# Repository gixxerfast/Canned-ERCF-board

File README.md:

# Canned-ERCF-board v1.0-beta2
Enraged Rabbit Carrot Feeder CAN-FD expansion board for Duet3

The Canned ERCF board is a general purpose Duet 3 CAN extansion board but specifically made to support the [ERCF](https://github.com/EtteGit/EnragedRabbitProject) multifilament feeder system based on the [ERCF Easy Brd](https://github.com/Tircown/ERCF-easy-brd) by Tircown.

Check out the [Duet RRF ERCF macros](https://github.com/pfn/EnragedRabbitOnRRF?ref=https://coder.social) by pfn. With these macros you should be able to use a RRF equipped printer and run multi filament prints as with the original ERCF macros as long as you have enough ports and motors available.

The board uses a Atmel/Microchip SAM C21 microcontroller module with USB and CAN, the [Sammy-C21](https://www.chip45.com/products/sammy-c21-1.0_atmel_smart_arm_sam_module_samc21_usb_dual_can_duet3d.php) from [Chip45](https://www.chip45.com/).

The firmware is a modified version of the [Duet3Expansion Sammy-C21 firmware](https://github.com/Duet3D/Duet3Expansion) by [Duet3D](https://www.duet3d.com/)  

You can find the fork of the modfied Duet firmware [here](https://github.com/gixxerfast/Duet3Expansion/tree/cannedboard). As the versions are moving rapidly with the new RRF version 3.4 there's no guarantees that this will be kept in synch.

**Please note that this board will not work with the standard Duet Sammy firmware.**

The board features the following functions:

- Support for up to two TMC2209 stepsticks Stepper motor drivers with UART control
- 1500 mA 24V-5V efficient switching voltage regulator. 
- Three GPIO inputs 3.3V signal inputs that may be used for encoders and endstops with 3.3V source.
- One 3.3V PWM output for hobby micro servo control with 5V source. Note that the general advice is not to source power to the servo via the board but to have a separate 5V source.
- MCU Module. It's using the Atmel/Microchip ATSAMC21G18A based Sammy-C21 MCU-module
- Input over voltage protection up to 30V
- VIN voltage monitoring.
- Three led indicators for 3.3V, 5V and VIN (24V). Easy troubleshooting if missing a rail. 

As an extension this board has CAN-FD support and is connected to another Duet 3 board via the CAN bus. Firmware is updated via CAN and the DWC (Duet Web Control frontend) so the USB-port is not really used.

This board can be used with the Sammy-C21 Duet 3 extension board firmware together with my modified configuration file. No further modifications are required (to this date).

There's a 4.7 Kohms pullup resistor on the TX/RX UART line as the BTT TMC2209 stepsticks has a 20K ohms pulldown resistor on the same line. The Duet firmware will disable the UART line before reading and writing causing the the line to go low and therefore corrupt the UART messaging. With the 4.7 Kohms pullup resistor the line is kept high all the time and the communication can function undisturbed.

There are two pin pairs for the CAN bus so either the CAN-bus can be terminated by closing the solder brideg on the back of the board or it can be routed to the next board in the chain,

## BOM
Apart from the board as specified in the KiCad files with the SMT components which I have had mounted by JLCPCB, there a number of components needed to complete the board

- 1 x Sammy-C21 ATSAMC21G18A MCU module from [Chip45](https://www.chip45.com/) or [Filastruder](https://www.filastruder.com/products/sammy-c21-v1-0-duet3d-module)
- 2 x BTT TMC2209 stepstick modules
- 1 x LMP78_05-1.5 or compatible DC-DC voltage converter
- 2 x 16 pin PCB connection headers
- 4 x 8 pin PCB connection headers
- 2 x 2 pin PCB connection headers
- 2 x 2 pin MOLEX KK254 (or equivalent) male PCB connectors
- 4 x 3 pin Molex KK254 (or equivalent) male PCB connectors
- 2 x 4 pin Molex KK254 (or equivalent) male PCB connectors
- 1 x 2 pin Phoenix 5.08 Screw connector. Part # 277-1247-ND or eqivalent

### Disclaimer 
This is work in progress and it's right now under development and there may exist issues with this version that may or may not be corrected in the next version. It's based on many parts over which I have no control over at all. I take no responsibilty whatsoever for the functionality or safety and I claim the right to not inform about anything about this product known to me now or in the future. This is soley at your own risk and I accept no responsiblity, financially or otherwise, if it causes your controller board to break, your house to burn down, your wife to divorce you, if it simply doesn't work at all or any other scenario possible in any multiverse. If you do not accept that all responibility for use of this product is your own, please don't download, build or use it.

## License - Open hardware / Open software
This project and its content is realeased under the [GPLv3 license](https://www.gnu.org/licenses/gpl-3.0.html)

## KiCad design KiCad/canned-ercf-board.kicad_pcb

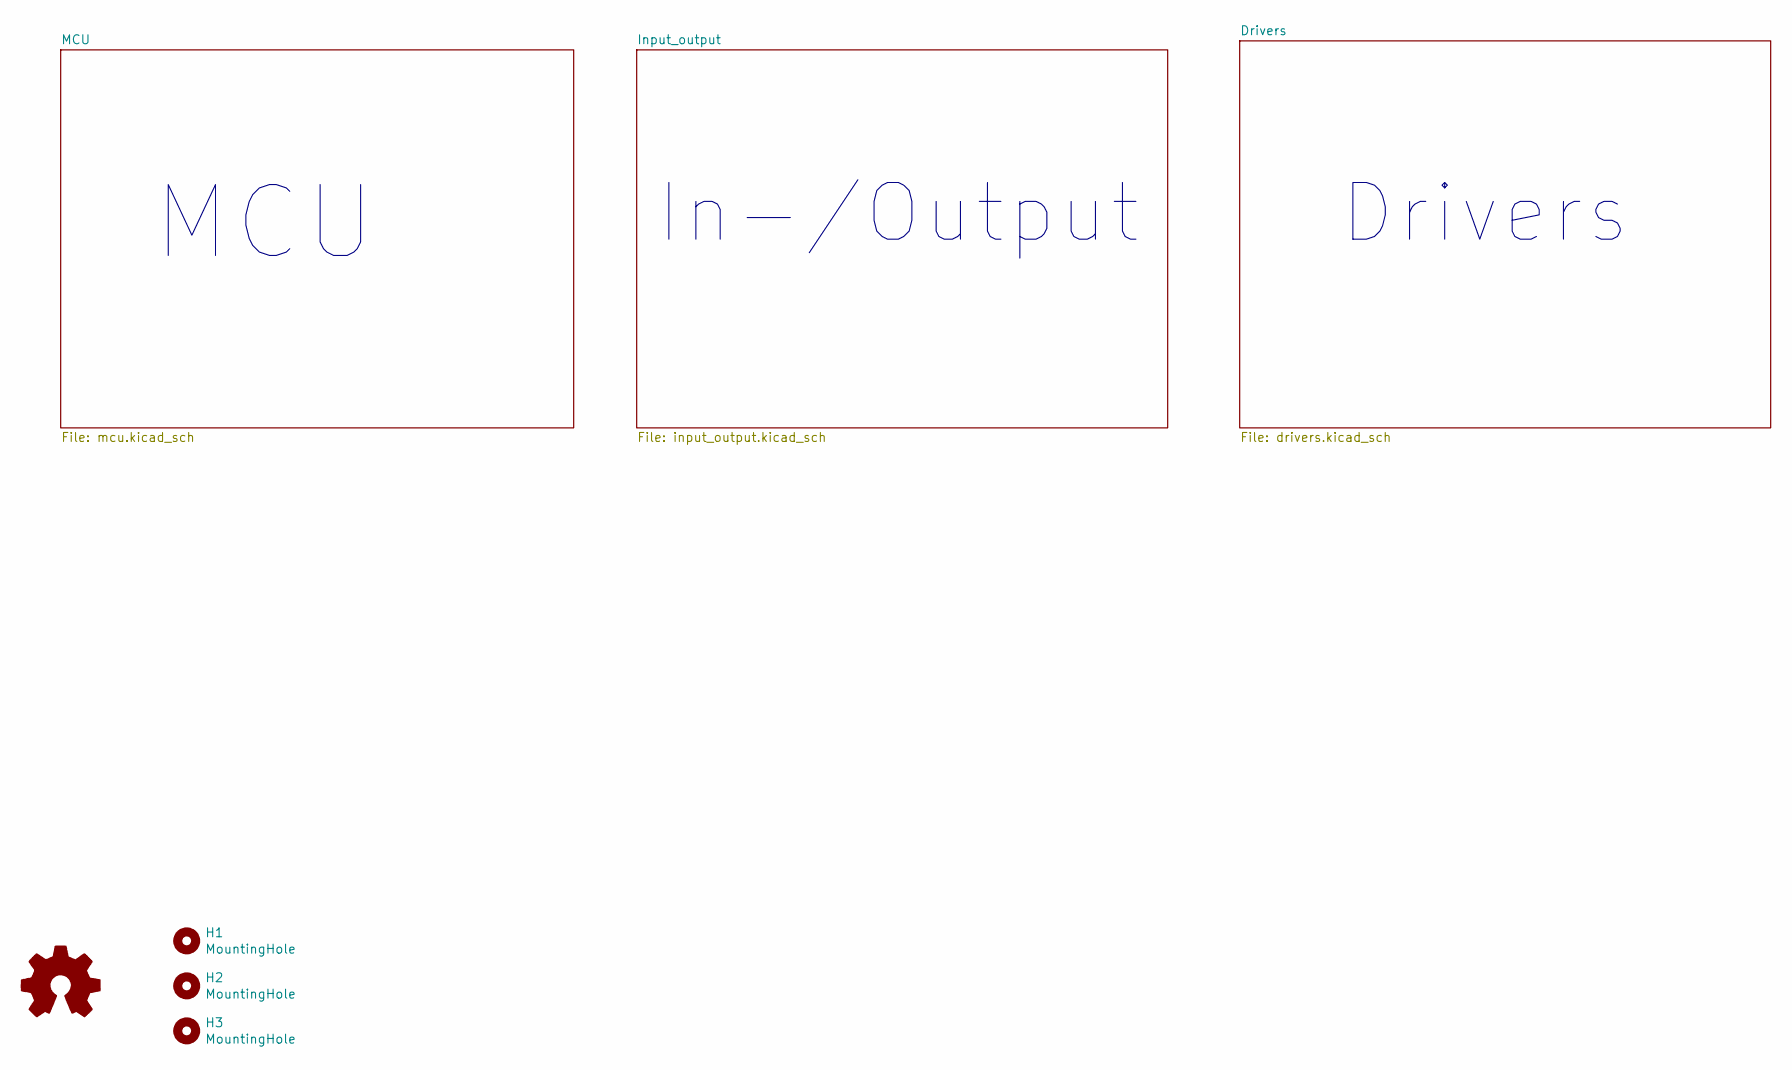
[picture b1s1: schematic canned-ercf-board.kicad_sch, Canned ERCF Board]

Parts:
H1, H2, H3: MountingHole; MountingHole_3.2mm_M3
L1: Logo_Open_Hardware_Small; OSHW-Logo2_7.3x6mm_SilkScreen

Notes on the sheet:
MCU
Drivers
In-/Output

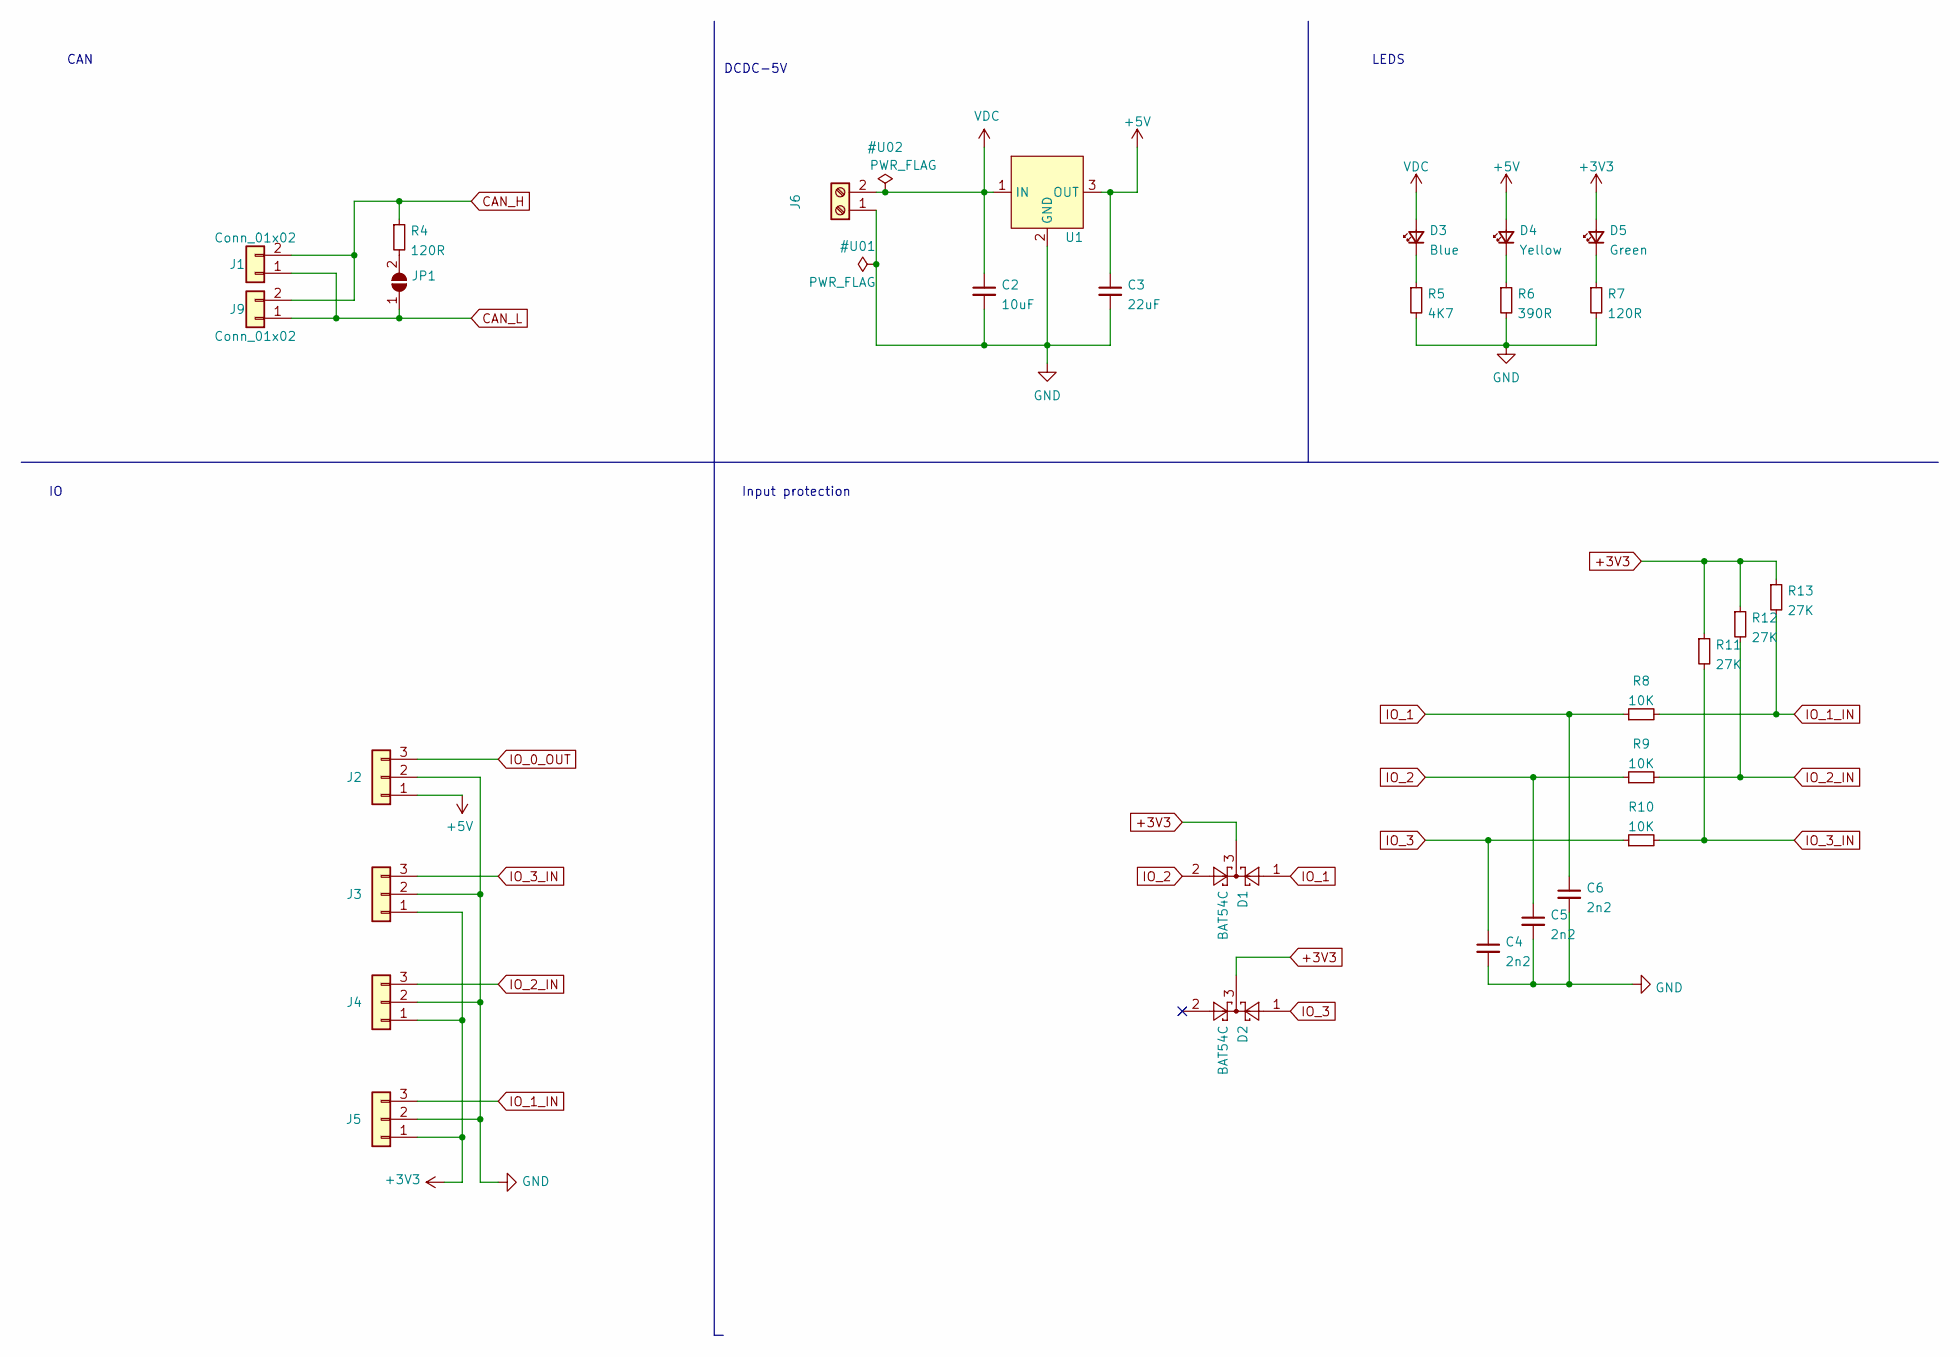
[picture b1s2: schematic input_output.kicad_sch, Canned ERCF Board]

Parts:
C2: 10uF; C_0805_2012Metric; Part GRM21BR61H106KE43L; LCSC C440198
C3: 22uF; C_0805_2012Metric; Part CL21A226MAQNNNE; LCSC C45783
C4, C5, C6: 2n2; C_0603_1608Metric; Part 0603B222K500NT; LCSC C1604
D1, D2: BAT54C; SOT-23; Part BAT54C,215; LCSC C37704
D3: Blue; LED_0603_1608Metric; Part 19-217/BHC-ZL1M2RY/3T; LCSC C72041
D4: Yellow; LED_0603_1608Metric; Part 19-213/Y2C-CQ2R2L/3T(CY); LCSC C72038
D5: Green; LED_0603_1608Metric; Part 19-217/GHC-YR1S2/3T; LCSC C72043
J1, J9: Conn_01x02; Molex_KK-254_AE-6410-02A_1x02_P2.54mm_Vertical
J2, J3, J4, J5: Conn_01x03_Male; Molex_KK-254_AE-6410-03A_1x03_P2.54mm_Vertical
J6: Screw_Terminal_01x02; TerminalBlock_bornier-2_P5.08mm_2; Part 1729128; LCSC C91153
JP1: SolderJumper_2_Open; SolderJumper-2_P1.3mm_Open_TrianglePad1.0x1.5mm
R4, R7: 120R; R_0603_1608Metric; Part 0603WAF1200T5E; LCSC C22787
R5: 4K7; R_0603_1608Metric; Part 0603WAF4701T5E; LCSC C23162
R6: 390R; R_0603_1608Metric; Part 0603WAF3900T5E; LCSC C23151
R8, R9, R10: 10K; R_0603_1608Metric; Part 0603WAF1002T5E; LCSC C25804
R11, R12, R13: 27K; R_0603_1608Metric; Part 0603WAF2702T5E; LCSC C22967
U1: Switching_Regulator_LMP78_05-1.5; Switching_regulator_POL_LMP78_1.5

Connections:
+5V: C3.1, D4.2 (A), J2.1, U1.3 (OUT); also elsewhere on the board
CAN_H: J1.2, J9.2, R4.1; also elsewhere on the board
CAN_L: J1.1, J9.1, JP1.1 (A); also elsewhere on the board
IO_0_OUT: J2.3; also elsewhere on the board
IO_1: C6.1, D1.1, R8.1; also elsewhere on the board
IO_1_IN: J5.3, R8.2, R13.2
IO_2: C5.1, D1.2, R9.1; also elsewhere on the board
IO_2_IN: J4.3, R9.2, R12.2
IO_3: C4.1, D2.1, R10.1; also elsewhere on the board
IO_3_IN: J3.3, R10.2, R11.2
unnamed: D3.1 (K), R5.1
unnamed: D4.1 (K), R6.1
unnamed: D5.1 (K), R7.1
unnamed: JP1.2 (B), R4.2

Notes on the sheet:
CAN
Input protection
LEDS
DCDC-5V

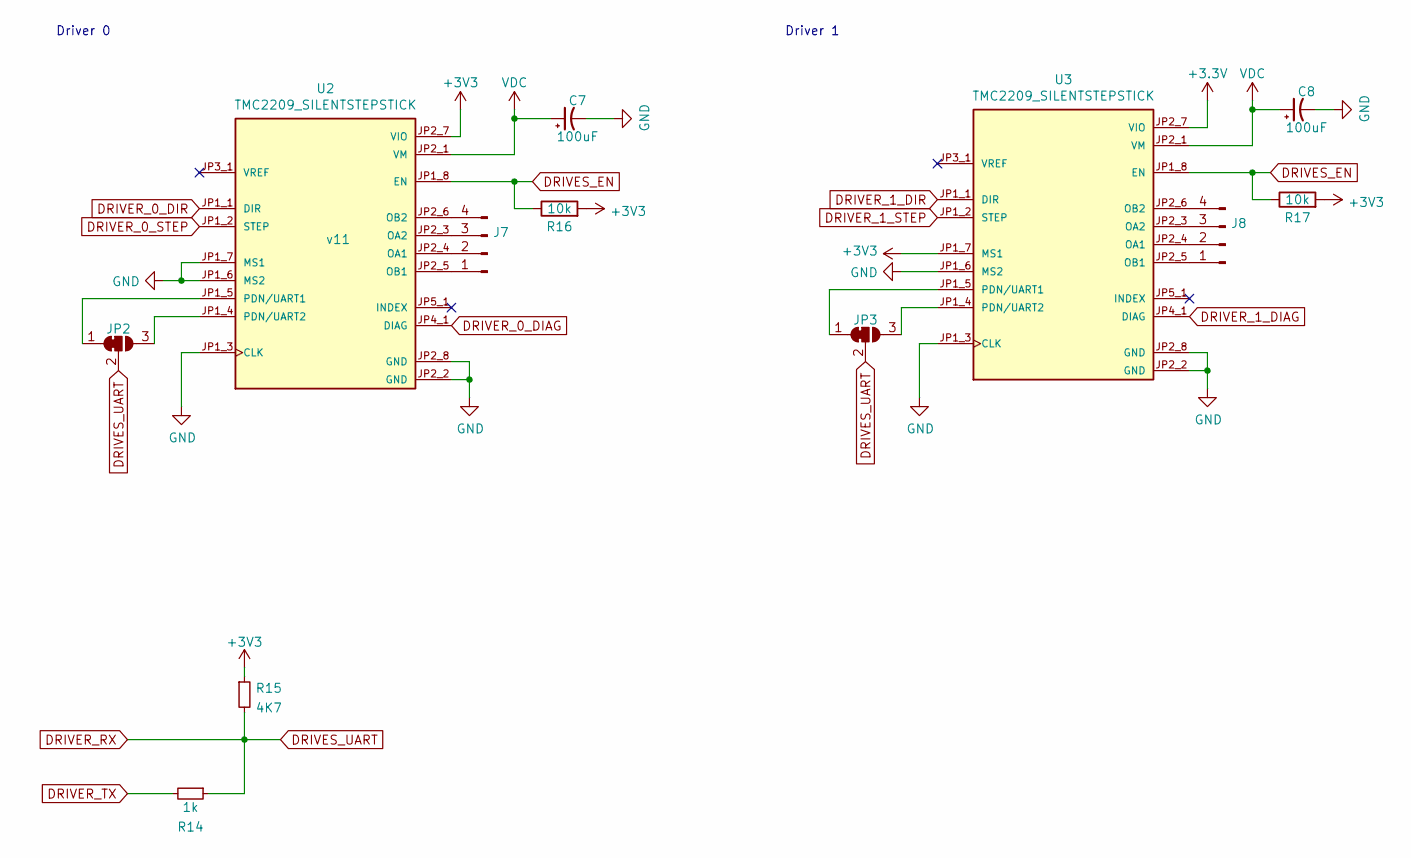
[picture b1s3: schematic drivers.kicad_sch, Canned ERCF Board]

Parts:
C7, C8: 100uF; CP_Elec_6.3x7.7; Part RT1V101M0607; LCSC C267470
J7, J8: Conn_01x04_Male; Molex_KK-254_AE-6410-04A_1x04_P2.54mm_Vertical
JP2, JP3: SolderJumper_3_Bridged12; SolderJumper-3_P1.3mm_Bridged12_RoundedPad1.0x1.5mm
R14: 1k; R_0603_1608Metric; Part 0603WAF1001T5E; LCSC C21190
R15: 4K7; R_0603_1608Metric; Part 0603WAF4702T5E; LCSC C23162
R16, R17: 10k; R_0603_1608Metric; Part 0603WAF1002T5E; LCSC C25804
U2, U3: TMC2209_SILENTSTEPSTICK; MODULE_TMC2209_SILENTSTEPSTICK; PARTREV v11

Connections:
DRIVER_0_DIAG: U2.JP4_1 (DIAG); also elsewhere on the board
DRIVER_0_DIR: U2.JP1_1 (DIR); also elsewhere on the board
DRIVER_0_STEP: U2.JP1_2 (STEP); also elsewhere on the board
DRIVER_1_DIAG: U3.JP4_1 (DIAG); also elsewhere on the board
DRIVER_1_DIR: U3.JP1_1 (DIR); also elsewhere on the board
DRIVER_1_STEP: U3.JP1_2 (STEP); also elsewhere on the board
DRIVER_RX: JP2.2 (C), JP3.2 (C), R14.1, R15.2; also elsewhere on the board
DRIVER_TX: R14.2; also elsewhere on the board
DRIVES_EN: R16.1, R17.1, U2.JP1_8 (EN), U3.JP1_8 (EN); also elsewhere on the board
unnamed: J7.1, U2.JP2_5 (OB1)
unnamed: J7.2, U2.JP2_4 (OA1)
unnamed: J7.3, U2.JP2_3 (OA2)
unnamed: J7.4, U2.JP2_6 (OB2)
unnamed: J8.1, U3.JP2_5 (OB1)
unnamed: J8.2, U3.JP2_4 (OA1)
unnamed: J8.3, U3.JP2_3 (OA2)
unnamed: J8.4, U3.JP2_6 (OB2)
unnamed: JP2.1 (A), U2.JP1_5 (PDN/UART1)
unnamed: JP2.3 (B), U2.JP1_4 (PDN/UART2)
unnamed: JP3.1 (A), U3.JP1_5 (PDN/UART1)
unnamed: JP3.3 (B), U3.JP1_4 (PDN/UART2)

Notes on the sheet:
Driver 1
Driver 0

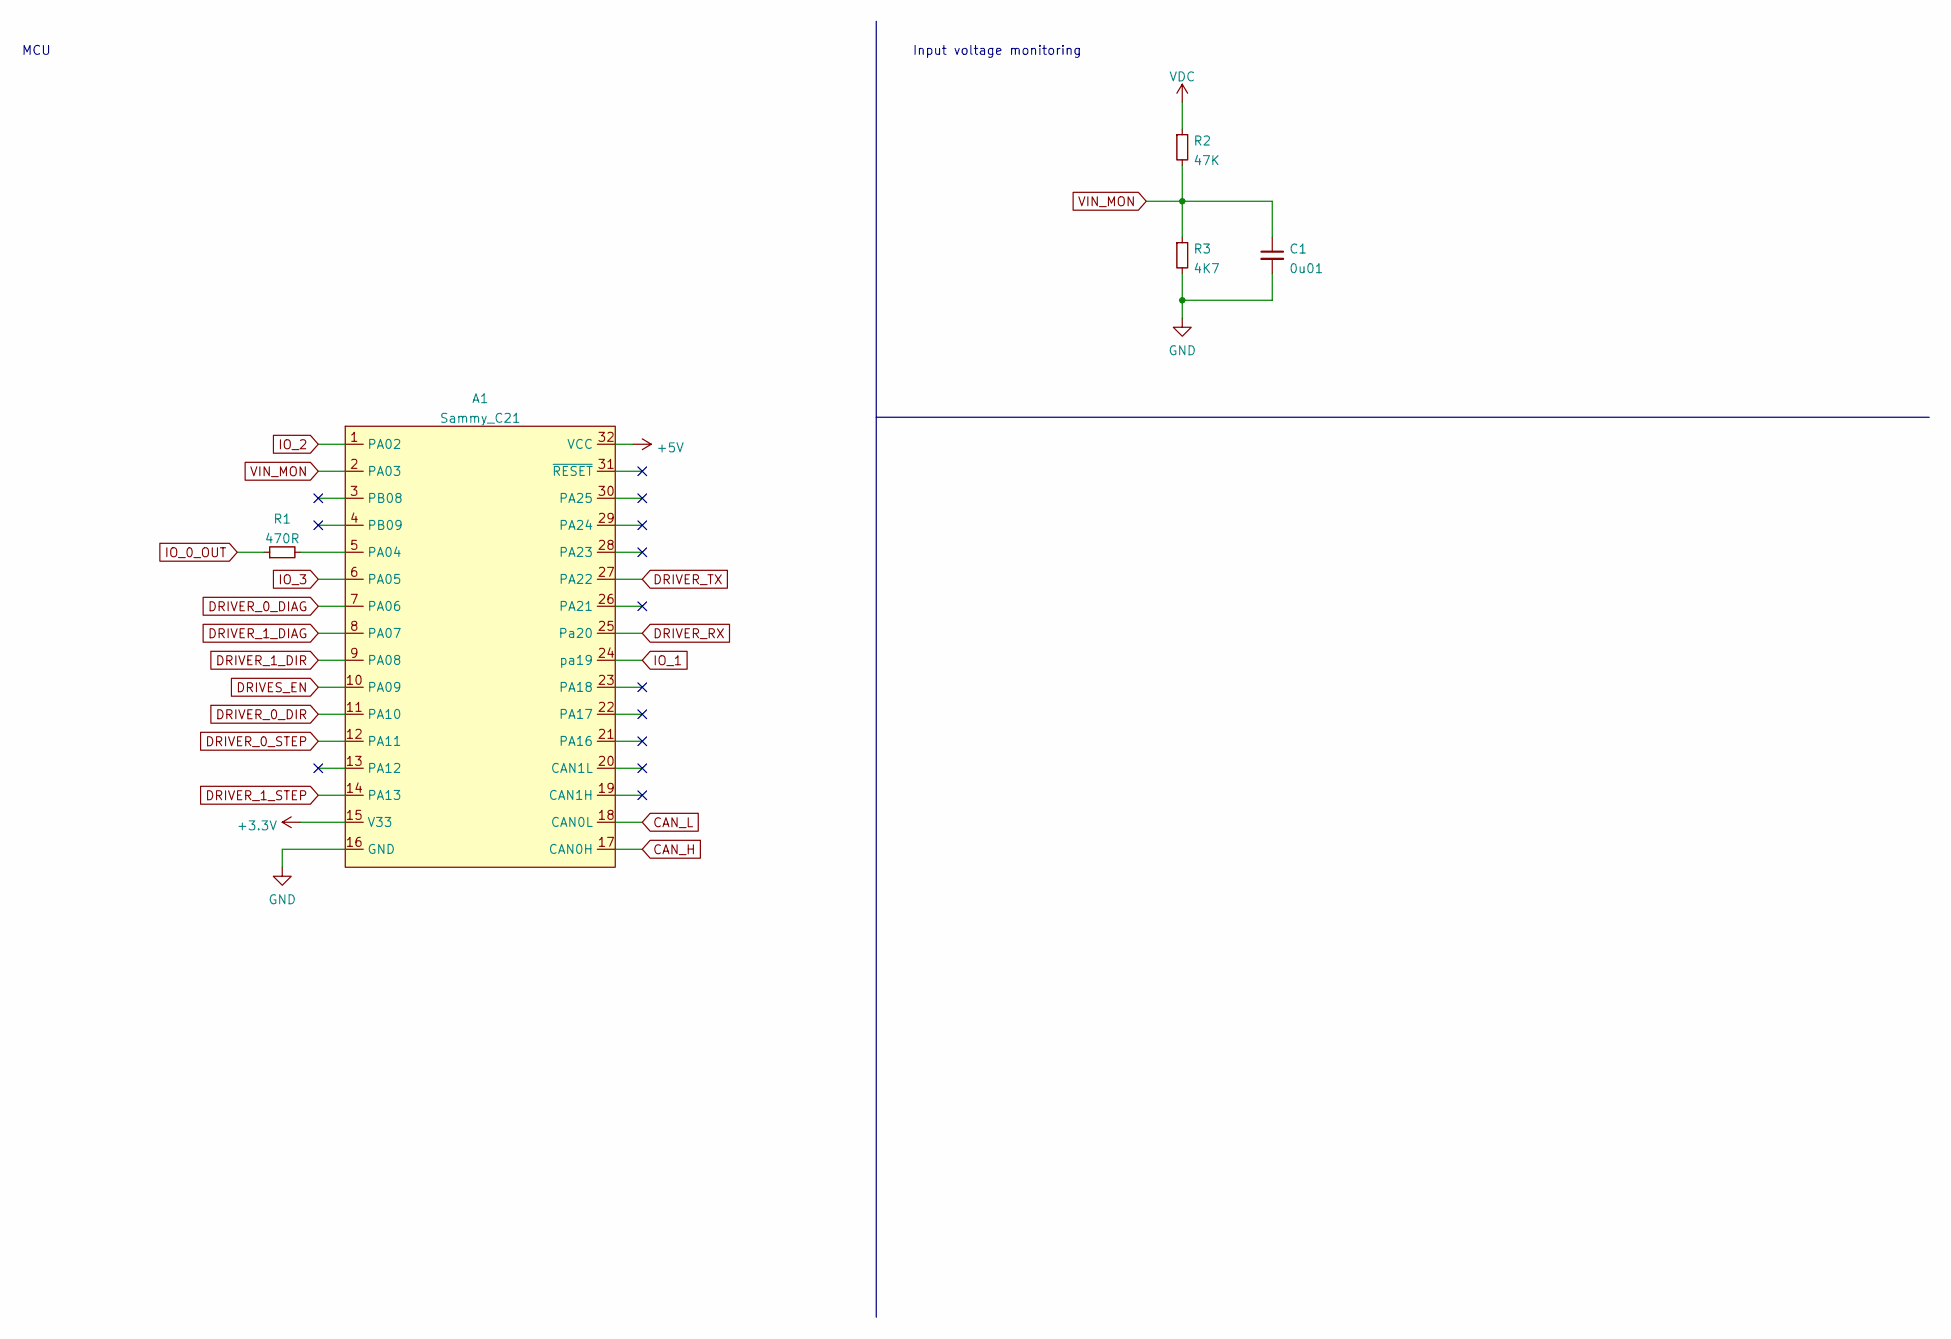
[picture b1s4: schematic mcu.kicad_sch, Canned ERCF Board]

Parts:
A1: Sammy_C21; Sammy_C21_Module_DIL32_2.54
C1: 0u01; C_0603_1608Metric; Part 0603B103K500NT; LCSC C57112
R1: 470R; R_0603_1608Metric; Part 0603WAF4700T5E; LCSC C23179
R2: 47K; R_0603_1608Metric; Part 0603WAF4702T5E; LCSC C25819
R3: 4K7; R_0603_1608Metric; Part 0603WAF4701T5E; LCSC C23162

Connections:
+5V: A1.32 (VCC); also elsewhere on the board
CAN_H: A1.17 (CAN0H); also elsewhere on the board
CAN_L: A1.18 (CAN0L); also elsewhere on the board
DRIVER_0_DIAG: A1.7 (PA06); also elsewhere on the board
DRIVER_0_DIR: A1.11 (PA10); also elsewhere on the board
DRIVER_0_STEP: A1.12 (PA11); also elsewhere on the board
DRIVER_1_DIAG: A1.8 (PA07); also elsewhere on the board
DRIVER_1_DIR: A1.9 (PA08); also elsewhere on the board
DRIVER_1_STEP: A1.14 (PA13); also elsewhere on the board
DRIVER_RX: A1.25 (Pa20); also elsewhere on the board
DRIVER_TX: A1.27 (PA22); also elsewhere on the board
DRIVES_EN: A1.10 (PA09); also elsewhere on the board
IO_0_OUT: R1.1; also elsewhere on the board
IO_1: A1.24 (pa19); also elsewhere on the board
IO_2: A1.1 (PA02); also elsewhere on the board
IO_3: A1.6 (PA05); also elsewhere on the board
unnamed: A1.5 (PA04), R1.2
VIN_MON: A1.2 (PA03), C1.1, R2.2, R3.1

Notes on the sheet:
Input voltage monitoring
MCU

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
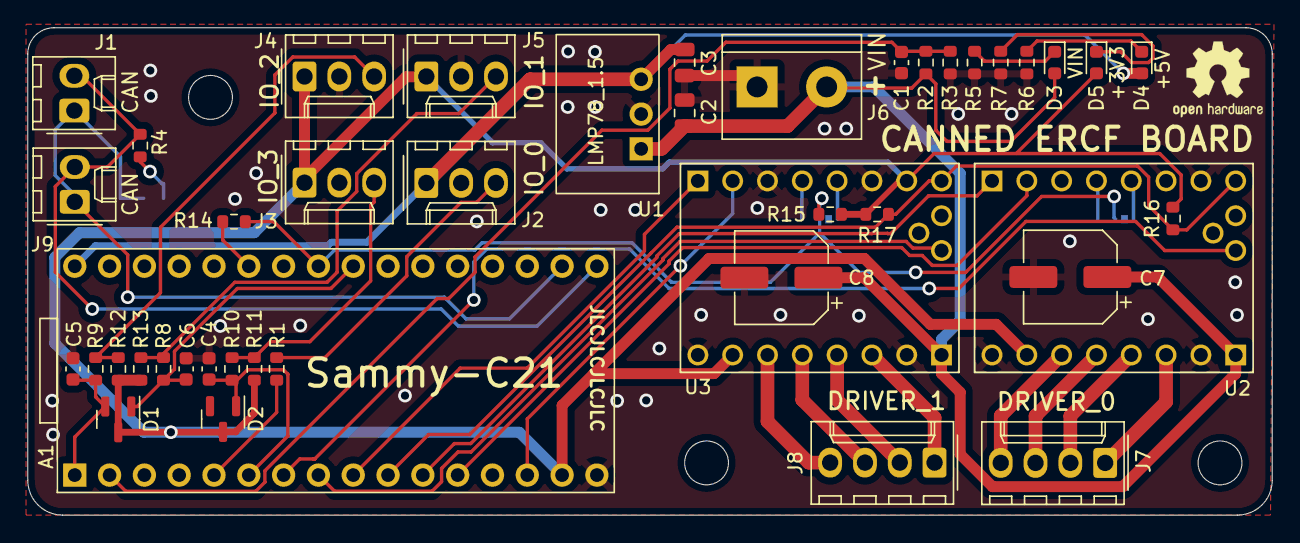
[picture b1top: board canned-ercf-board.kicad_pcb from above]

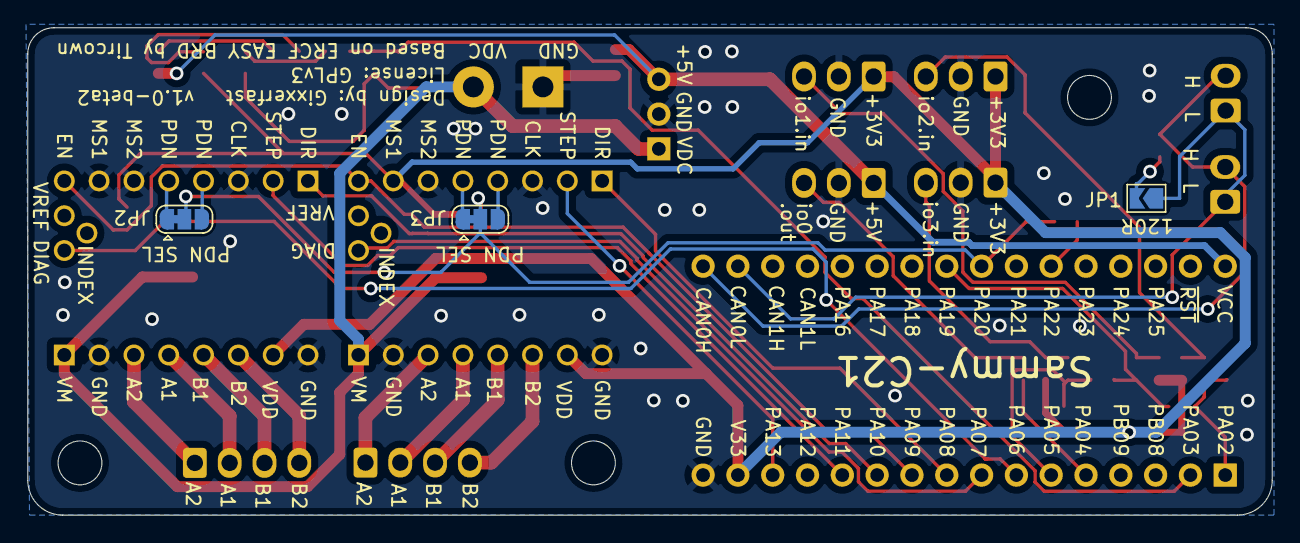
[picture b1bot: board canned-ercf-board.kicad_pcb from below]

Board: 2 copper layers, 90.8 x 35.6 mm, 50 parts (3 on the bottom side), 40 nets.

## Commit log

2022-02-09 First version in Git
2022-02-09 Added first version of readme
2022-02-28 v1.0-beta2
2022-03-01 Removed old zip and added new version of readme
2022-03-01 Added new photo
2022-03-01 Cleaned up
2022-03-01 Updated description
2022-03-01 added link to pfn ERCF macros in the README

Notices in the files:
KiCad/canned-ercf-board.kicad_pcb:
License: GPLv3
